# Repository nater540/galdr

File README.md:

# Galdr

**Galdr** is a compact desktop CNC milling system: custom [grblHAL](https://github.com/grblHAL)-compatible firmware
for an **ESP32-S3** motion controller, plus **skirnir**, a native desktop GCode sender that streams to it over USB.
It is general-purpose 2.5D/3-axis milling, with PCB isolation milling and no-touch-plate probing as a first-class
use case.

The firmware drives three stepper axes through silent [TMC2209](https://www.trinamic.com/) drivers and a WS55-220
spindle, speaks the grbl v1.1 / grblHAL streaming protocol, and is built around a strict hardware-abstraction boundary
so the entire motion pipeline — GCode parsing, look-ahead planning, the homing state machine, coordinate systems —
is pure `no_std` Rust that compiles and unit-tests on the host with stock Rust (600+ tests, no hardware required).

> *skirnir, the host-side GCode sender: the connection toolbar and state badge, the work/machine DRO and jog pad,
> feed/spindle/rapid overrides, a Z-probe panel, X/Y/Z endstop (`LIMITS`) indicators, the program console, and the
> toolpath viewport rendering a loaded program.*

---

## Workspace layout

Galdr is a Cargo workspace of four crates:

| Crate | Role |
|-------|------|
| [`crates/firmware-core`](crates/firmware-core) | Pure, `no_std`, **host-tested** logic: GCode parser, motion planner, segment generator, grblHAL protocol/state machine, the homing state machine, coordinate systems, settings model, and the TMC2209 codec. No esp-hal dependency. |
| [`crates/firmware`](crates/firmware) | The **ESP32-S3** binary wiring `firmware-core` to the hardware (esp-hal 1.0 + Embassy on the esp-rtos host): USB CDC comms, the dual-core task split, RMT step generation, the TMC UART bus, flash persistence, and the limit-switch inputs. |
| [`crates/galdr-proto`](crates/galdr-proto) | The shared Protocol Buffers schema (micropb) for the settings/coordinate wire format — used by both the firmware flash records and the `$PBX` host-sync channel. |
| [`crates/skirnir`](crates/skirnir) | The native GCode sender: an **egui/eframe** GUI on top of a framework-agnostic `tokio-serial` streaming engine. |

## Hardware

| Subsystem | Detail |
|-----------|--------|
| Controller | ESP32-S3 (Xtensa LX7), native USB Serial/JTAG to the host |
| Steppers | 3× X/Y/Z via TMC2209 on a shared single-wire UART bus (CRC8-ATM datagrams) |
| Step generation | One dedicated RMT TX channel per axis (ch0/1/2) |
| Endstops | Normally-closed micro-switches on GPIO10/11/12, internal pull-ups, broken-wire fail-safe |
| Spindle | WS55-220 via LEDC PWM → RC + op-amp → 0–10 V |

See [`docs/00-architecture.md`](docs/00-architecture.md) for the full hardware/GPIO manifest and firmware design
(DOC-00 – DOC-09).

## Status

The firmware (`firmware-core` + `firmware` + `galdr-proto`) is substantially implemented and host-tested:

- ✅ GCode → planner → motion pipeline (look-ahead, junction-deviation cornering, trapezoidal segment generation)
- ✅ grblHAL streaming protocol (character-counting flow control, real-time commands, `<...>` status reports)
- ✅ TMC2209 driver (current scaling, register init, CRC8-ATM)
- ✅ Settings + coordinate-system persistence (flash + `$PBX` host sync)
- ✅ G38.x probing, jogging, feed/rapid/spindle overrides
- ✅ `$H` homing cycle, hard/soft limits, and limit-switch `Pn:` status reporting (DOC-06)

**Not yet hardware-verified:** the DOC-06 homing/limit *logic* is fully host-tested, but its hardware boundary — the
rising-edge limit IRQ + debounce, the NC broken-wire fail-safe, and real seek/locate timing — is compile-checked only.
Run [`docs/homing-bench-checklist.md`](docs/homing-bench-checklist.md) on the board to validate it.

**Stubbed (logic exists, no peripheral output yet):** spindle PWM output (DOC-07) and the coolant GPIO.

skirnir is a working app: connection + reconnection, the streaming engine, `<...>`/`Pn:` status parsing, a DRO, jog
controls, override controls, a program console, and endstop indicators.

## Build & test

The workspace root is the repo root. Host crates build with stock Rust; the firmware needs the Espressif toolchain.

### Host (firmware-core, skirnir, galdr-proto)

```sh
cargo build                         # builds the host-buildable crates (firmware is excluded)
cargo test                          # host tests; add RUSTFLAGS="-D warnings" to match CI
cargo run -p skirnir                # launch the skirnir GUI
cargo run -p skirnir -- --cli <port>   # headless streaming smoke path
```

`firmware` is excluded from `default-members`, so the bare commands above stay on the host toolchain and skip it.
`--workspace`/`--all` override that — pass `--exclude firmware` with those flags.

### Firmware (ESP32-S3 / Xtensa LX7)

The Xtensa ISA needs Espressif's Rust fork:

```sh
cargo install espup
espup install
source $HOME/export-esp.sh          # source in every shell before firmware builds
```

The `justfile` wraps the toolchain env and the crate-scoped target/runner:

```sh
just build        # cargo build for Xtensa (e.g. `just build --release` / `--features defmt`)
just flash        # build + flash + serial monitor (espflash)
just monitor      # attach the serial monitor only
```

> See [`CLAUDE.md`](CLAUDE.md) for the full build notes, including the `esp-bootloader-esp-idf = "=0.4.0"` pin
> required with esp-hal 1.0.

## Design docs

`docs/` is the authoritative design spec — read the relevant doc before extending a subsystem.

| Doc | Covers |
|-----|--------|
| [`docs/00-architecture.md`](docs/00-architecture.md) | Full firmware spec (DOC-00 – DOC-09): hardware/GPIO manifest, Embassy task split, RMT step generation, TMC2209 driver, GCode parser, motion planner, homing, spindle, USB CDC, testing. **Start here.** |
| [`docs/gcode-streaming.md`](docs/gcode-streaming.md) | grblHAL streaming protocol: flow control, real-time commands, status reports, handshake, `$`-settings, probing. |
| [`docs/tlo-offsets.md`](docs/tlo-offsets.md) | Tool-length-offset / Z-probe workflow (G38.x, WPos/MPos/WCO/TLO) for no-touch-plate probing — single-tool re-zero and multi-tool reference-tool offsets (PCB isolation is one worked example). |
| [`docs/native-app.md`](docs/native-app.md) + [`docs/skirnir-design-brief.md`](docs/skirnir-design-brief.md) | skirnir design and UI brief (the source under `crates/skirnir/src/` is the truth). |
| [`docs/homing-research-findings.md`](docs/homing-research-findings.md) | The verified grblHAL homing/limit behavioral contract the implementation follows. |
| [`docs/homing-bench-checklist.md`](docs/homing-bench-checklist.md) | Hardware-in-the-loop bring-up procedure for the homing cycle + limit switches. |

## Conventions

- Two-space indentation (`.editorconfig`), LF endings, final newline.
- No `unwrap()`/`expect()` in library code; `#![deny(unsafe_code)]` in library crates; `#![deny(warnings)]` in CI.
- All hardware access goes behind traits (`StepSink`, `TmcBus`, `ProbeInput`, `DigitalIn`, …) so the logic stays
  host-testable; only the firmware wiring layer touches esp-hal.

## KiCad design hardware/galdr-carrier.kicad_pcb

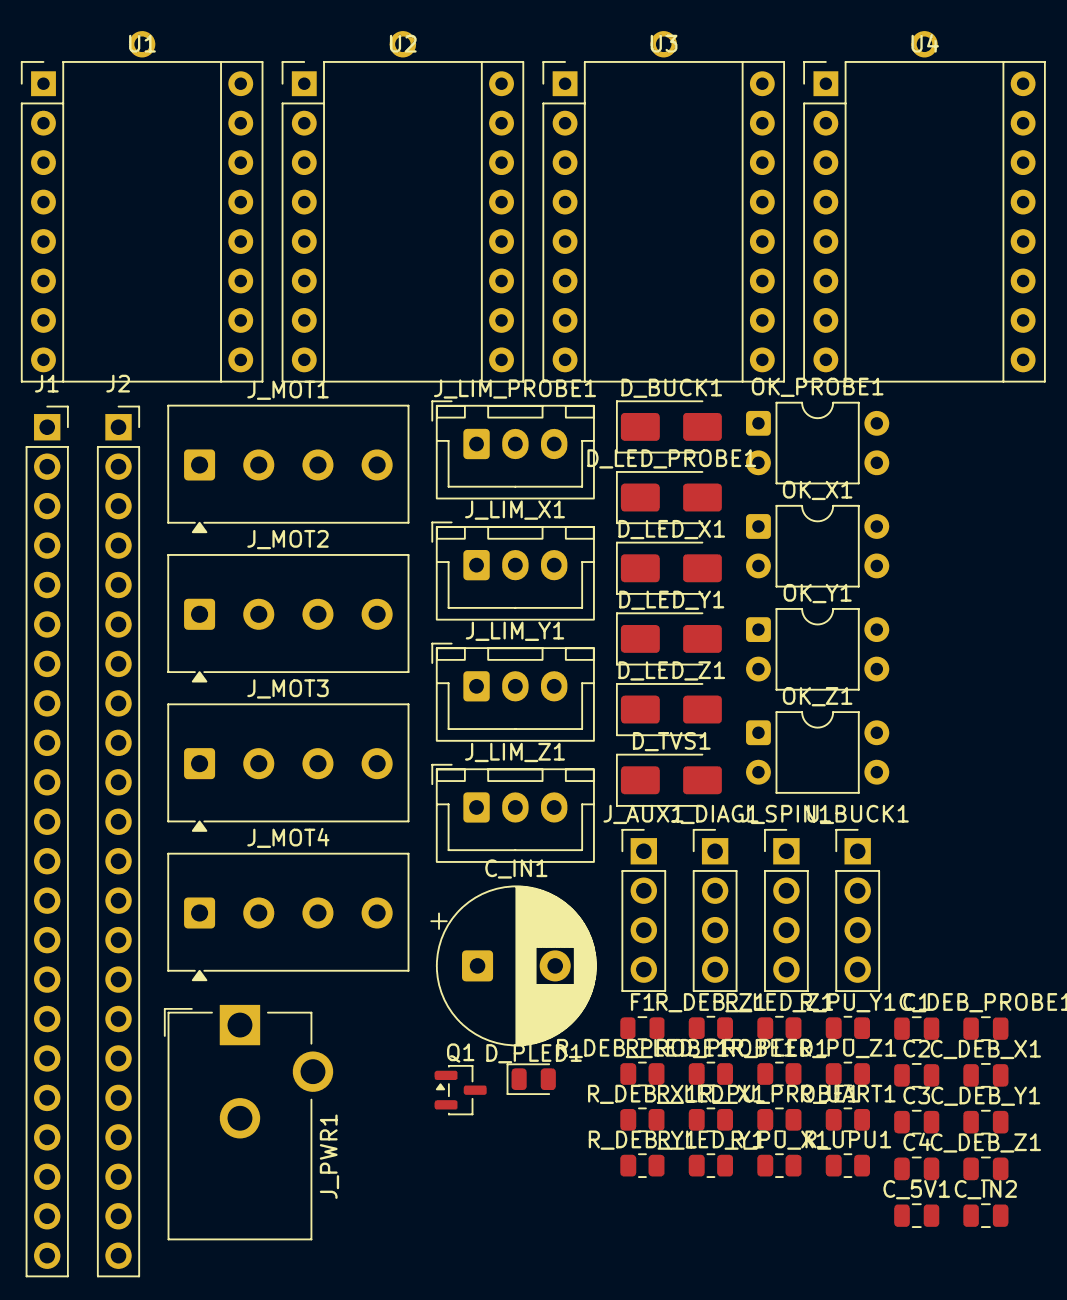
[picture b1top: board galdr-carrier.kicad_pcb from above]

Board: 2 copper layers, 58 parts (0 on the bottom side), 59 nets, no tracks yet.

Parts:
C1, C2, C3, C4: 100n; C_0805_2012Metric
C_5V1: 10u; C_0805_2012Metric
C_DEB_PROBE1: 100n; C_0805_2012Metric
C_DEB_X1: 100n; C_0805_2012Metric
C_DEB_Y1: 100n; C_0805_2012Metric
C_DEB_Z1: 100n; C_0805_2012Metric
C_IN1: 470u/35V; CP_Radial_D10.0mm_P5.00mm
C_IN2: 100n; C_0805_2012Metric
D_BUCK1: SS34; D_SMA
D_LED_PROBE1: 1N4148; D_SMA
D_LED_X1: 1N4148; D_SMA
D_LED_Y1: 1N4148; D_SMA
D_LED_Z1: 1N4148; D_SMA
D_PLED1: PWR; LED_0805_2012Metric
D_TVS1: SMAJ16A; D_SMA
F1: 3A; Fuse_0805_2012Metric
J1: ESP32-S3 DevBoard L; PinSocket_1x22_P2.54mm_Vertical
J2: ESP32-S3 DevBoard R; PinSocket_1x22_P2.54mm_Vertical
J_AUX1: AUX_CTRL; PinHeader_1x04_P2.54mm_Vertical
J_DIAG1: DIAG; PinHeader_1x04_P2.54mm_Vertical
J_LIM_PROBE1: LIM_PROBE; JST_XH_B3B-XH-A_1x03_P2.50mm_Vertical
J_LIM_X1: LIM_X; JST_XH_B3B-XH-A_1x03_P2.50mm_Vertical
J_LIM_Y1: LIM_Y; JST_XH_B3B-XH-A_1x03_P2.50mm_Vertical
J_LIM_Z1: LIM_Z; JST_XH_B3B-XH-A_1x03_P2.50mm_Vertical
J_MOT1: MOTOR_X; TerminalBlock_Phoenix_MKDS-1-4-3.81_1x04_P3.81mm_Horizontal
J_MOT2: MOTOR_Y; TerminalBlock_Phoenix_MKDS-1-4-3.81_1x04_P3.81mm_Horizontal
J_MOT3: MOTOR_Z; TerminalBlock_Phoenix_MKDS-1-4-3.81_1x04_P3.81mm_Horizontal
J_MOT4: MOTOR_A; TerminalBlock_Phoenix_MKDS-1-4-3.81_1x04_P3.81mm_Horizontal
J_PWR1: DC_12V_5.5x2.5; BarrelJack_CUI_PJ-102AH_Horizontal
J_SPIN1: SPINDLE; PinHeader_1x04_P2.54mm_Vertical
OK_PROBE1: PC817; DIP-4_W7.62mm
OK_X1: PC817; DIP-4_W7.62mm
OK_Y1: PC817; DIP-4_W7.62mm
OK_Z1: PC817; DIP-4_W7.62mm
Q1: AO3401(GSD); SOT-23
R_DEB_PROBE1: 1k; R_0805_2012Metric
R_DEB_X1: 1k; R_0805_2012Metric
R_DEB_Y1: 1k; R_0805_2012Metric
R_DEB_Z1: 1k; R_0805_2012Metric
R_LED_PROBE1: 680; R_0805_2012Metric
R_LED_X1: 680; R_0805_2012Metric
R_LED_Y1: 680; R_0805_2012Metric
R_LED_Z1: 680; R_0805_2012Metric
R_PLED1: 4k7; R_0805_2012Metric
R_PU_PROBE1: 10k; R_0805_2012Metric
R_PU_X1: 10k; R_0805_2012Metric
R_PU_Y1: 10k; R_0805_2012Metric
R_PU_Z1: 10k; R_0805_2012Metric
R_UART1: 1k; R_0805_2012Metric
R_UPU1: 20k; R_0805_2012Metric
U1, U2, U3, U4: BTT TMC2209 V1.3; TMC2209_StepStick_Socket
U_BUCK1: MP1584_12to5; PinHeader_1x04_P2.54mm_Vertical

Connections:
+3V3: J1.1 (3V3), J1.2 (3V3), J_AUX1.3, R_PU_PROBE1.1, R_PU_X1.1, R_PU_Y1.1, R_PU_Z1.1, R_UPU1.1, U1.10 (VIO), U2.2 (MS1), U2.10 (VIO), U3.3 (MS2), U3.10 (VIO), U4.2 (MS1), U4.3 (MS2), U4.10 (VIO)
+5V: C_5V1.1, D_BUCK1.1 (K), J1.21 (5V0)
+5V_BUCK: D_BUCK1.2 (A), U_BUCK1.3
+12V: C1.1, C2.1, C3.1, C4.1, C_IN1.1, C_IN2.1, D_TVS1.1 (A1), J_LIM_PROBE1.1, J_LIM_X1.1, J_LIM_Y1.1, J_LIM_Z1.1, R_LED_PROBE1.1, R_LED_X1.1, R_LED_Y1.1, R_LED_Z1.1, R_PLED1.1, U1.16 (VM), U2.16 (VM), U3.16 (VM), U4.16 (VM), U_BUCK1.1
A_A1: J_MOT4.1, U4.13 (A1)
A_A2: J_MOT4.2, U4.14 (A2)
A_B1: J_MOT4.3, U4.12 (B1)
A_B2: J_MOT4.4, U4.11 (B2)
A_DIAG: J_DIAG1.4, U4.17 (DIAG)
A_DIR: J2.6 (IO42), U4.8 (DIR)
A_STEP: J1.11 (IO18), U4.7 (STEP)
CYCSTART: J1.10 (IO17), J_AUX1.2
FHOLD: J1.9 (IO16), J_AUX1.1
GND: C1.2, C2.2, C3.2, C4.2, C_5V1.2, C_DEB_PROBE1.2, C_DEB_X1.2, C_DEB_Y1.2, C_DEB_Z1.2, C_IN1.2, C_IN2.2, D_PLED1.1 (K), D_TVS1.2 (A2), J1.22 (GND), J2.1 (GND), J2.21 (GND), J2.22 (GND), J_AUX1.4, J_LIM_PROBE1.3, J_LIM_X1.3, J_LIM_Y1.3, J_LIM_Z1.3, J_PWR1.2, J_SPIN1.4, OK_PROBE1.3, OK_X1.3, OK_Y1.3, OK_Z1.3, U1.2 (MS1), U1.3 (MS2), U1.6 (CLK), U1.9 (GND), U1.15 (GND), U2.3 (MS2), U2.6 (CLK), U2.9 (GND), U2.15 (GND), U3.2 (MS1), U3.6 (CLK), U3.9 (GND), U3.15 (GND), U4.6 (CLK), U4.9 (GND), U4.15 (GND), U_BUCK1.2, U_BUCK1.4
PLED_A: D_PLED1.2 (A), R_PLED1.2
PROBE: C_DEB_PROBE1.1, J2.18 (IO21), R_DEB_PROBE1.2
PROBE_COL: OK_PROBE1.4, R_DEB_PROBE1.1, R_PU_PROBE1.2
PROBE_LEDA: D_LED_PROBE1.1 (K), OK_PROBE1.1, R_LED_PROBE1.2
PROBE_SIG: D_LED_PROBE1.2 (A), J_LIM_PROBE1.2, OK_PROBE1.2
SPIN_DIR: J1.8 (IO15), J_SPIN1.3
SPIN_EN: J1.20 (IO14), J_SPIN1.2
SPIN_PWM: J1.19 (IO13), J_SPIN1.1
STEP_EN: J1.12 (IO8), U1.1 (EN), U2.1 (EN), U3.1 (EN), U4.1 (EN)
TMC_BUS: R_UART1.2, R_UPU1.2, U1.4 (RX), U1.5 (TX), U2.4 (RX), U2.5 (TX), U3.4 (RX), U3.5 (TX), U4.4 (RX), U4.5 (TX)
TMC_UART: J1.15 (IO9), R_UART1.1
VIN_RAW: F1.1, J_PWR1.1
X_A1: J_MOT1.1, U1.13 (A1)
X_A2: J_MOT1.2, U1.14 (A2)
X_B1: J_MOT1.3, U1.12 (B1)
X_B2: J_MOT1.4, U1.11 (B2)
X_COL: OK_X1.4, R_DEB_X1.1, R_PU_X1.2
X_DIAG: J_DIAG1.1, U1.17 (DIAG)
X_DIR: J1.5 (IO5), U1.8 (DIR)
X_LEDA: D_LED_X1.1 (K), OK_X1.1, R_LED_X1.2
X_LIM: C_DEB_X1.1, J1.16 (IO10), R_DEB_X1.2
X_SIG: D_LED_X1.2 (A), J_LIM_X1.2, OK_X1.2
X_STEP: J2.4 (IO1), U1.7 (STEP)
Y_A1: J_MOT2.1, U2.13 (A1)
Y_A2: J_MOT2.2, U2.14 (A2)
Y_B1: J_MOT2.3, U2.12 (B1)
Y_B2: J_MOT2.4, U2.11 (B2)
Y_COL: OK_Y1.4, R_DEB_Y1.1, R_PU_Y1.2
Y_DIAG: J_DIAG1.2, U2.17 (DIAG)
Y_DIR: J1.6 (IO6), U2.8 (DIR)
Y_LEDA: D_LED_Y1.1 (K), OK_Y1.1, R_LED_Y1.2
Y_LIM: C_DEB_Y1.1, J1.17 (IO11), R_DEB_Y1.2
Y_SIG: D_LED_Y1.2 (A), J_LIM_Y1.2, OK_Y1.2
Y_STEP: J2.5 (IO2), U2.7 (STEP)
Z_A1: J_MOT3.1, U3.13 (A1)
Z_A2: J_MOT3.2, U3.14 (A2)
Z_B1: J_MOT3.3, U3.12 (B1)
Z_B2: J_MOT3.4, U3.11 (B2)
Z_COL: OK_Z1.4, R_DEB_Z1.1, R_PU_Z1.2
Z_DIAG: J_DIAG1.3, U3.17 (DIAG)
Z_DIR: J1.7 (IO7), U3.8 (DIR)
Z_LEDA: D_LED_Z1.1 (K), OK_Z1.1, R_LED_Z1.2
Z_LIM: C_DEB_Z1.1, J1.18 (IO12), R_DEB_Z1.2
Z_SIG: D_LED_Z1.2 (A), J_LIM_Z1.2, OK_Z1.2
Z_STEP: J1.4 (IO4), U3.7 (STEP)

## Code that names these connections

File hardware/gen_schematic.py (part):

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           ref_xy=(EOX - 13, EOY - 36), val_xy=(EOX - 13, EOY - 33.5))
# pin number -> net  ('' => power port handled below, None entries => no_connect)
ESP_SIG = {  # left column
    "4": "Z_STEP", "5": "X_DIR", "6": "Y_DIR", "7": "Z_DIR", "8": "SPIN_DIR", "9": "FHOLD",
    "10": "CYCSTART", "11": "A_STEP", "12": "STEP_EN", "15": "TMC_UART", "16": "X_LIM",
    "17": "Y_LIM", "18": "Z_LIM", "19": "SPIN_PWM", "20": "SPIN_EN",
    # right column
    "26": "X_STEP", "27": "Y_STEP", "28": "A_DIR", "40": "PROBE"}
ESP_PWR = {"1": "+3V3", "2": "+3V3", "21": "+5V", "22": "GND", "23": "GND", "43": "GND", "44": "GND"}
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    t = place("Galdr:BTT_TMC2209", f"U{i+1}", "BTT TMC2209 V1.3", FP_TMC, ox, oy,
              ref_xy=(ox - 7, oy - 20.5), val_xy=(ox - 7, oy - 18))
    # left side: control signals + straps (stub left, then label/port)
    seg(*t["1"], t["1"][0] - 2.54, t["1"][1]); glabel("STEP_EN", t["1"][0] - 2.54, t["1"][1], 180)   # EN
    for strap_num in ("2", "3"):                                                                       # MS1/MS2
        seg(*t[strap_num], t[strap_num][0] - 2.54, t[strap_num][1]); pwr(ms[strap_num], t[strap_num][0] - 2.54, t[strap_num][1])
    # RX (4) + TX (5) both join the single-wire UART bus
    seg(*t["4"], t["4"][0] - 2.54, t["4"][1]); glabel("TMC_BUS", t["4"][0] - 2.54, t["4"][1], 180)
    seg(*t["5"], t["5"][0] - 2.54, t["5"][1]); glabel("TMC_BUS", t["5"][0] - 2.54, t["5"][1], 180)
    seg(*t["6"], t["6"][0] - 2.54, t["6"][1]); pwr("GND", t["6"][0] - 2.54, t["6"][1])                 # CLK -> GND
    seg(*t["7"], t["7"][0] - 2.54, t["7"][1]); glabel(f"{ax}_STEP", t["7"][0] - 2.54, t["7"][1], 180)
    seg(*t["8"], t["8"][0] - 2.54, t["8"][1]); glabel(f"{ax}_DIR", t["8"][0] - 2.54, t["8"][1], 180)
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# ---- TMC UART: series resistor to the bus + idle pull-up to +3V3 -------------
# R_UART converts the half-duplex single-wire UART; R_UPU idles the bus high. Both tie to the TMC_BUS node.
ru = place("Device:R", "R_UART", "1k", FP_R, 220, 56, 90)     # horizontal: pin2 left, pin1 right
seg(*ru["2"], ru["2"][0] - 2.54, ru["2"][1]); glabel("TMC_UART", ru["2"][0] - 2.54, ru["2"][1], 180)
rp = place("Device:R", "R_UPU", "20k", FP_R, 220, 48)         # vertical: pin1 top -> +3V3, pin2 bottom -> bus
seg(*rp["1"], rp["1"][0], rp["1"][1] - 2.54); pwr("+3V3", rp["1"][0], rp["1"][1] - 2.54)
# TMC_BUS node: join R_UART pin1 (right) and R_UPU pin2 (bottom) and emit a global label.
busx = ru["1"][0] + 2.54
seg(ru["1"][0], ru["1"][1], busx, ru["1"][1])
seg(rp["2"][0], rp["2"][1], rp["2"][0], ru["1"][1])
seg(rp["2"][0], ru["1"][1], busx, ru["1"][1])
junction(rp["2"][0], ru["1"][1])
glabel("TMC_BUS", busx, ru["1"][1], 0)

# ---- opto-isolated inputs: X / Y / Z limits + PROBE ------------------------
# Per channel: a field connector drives the PC817 LED through a current-limit resistor (anti-parallel signal diode
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    seg(*cdb["2"], cdb["2"][0], cdb["2"][1] + 2.54); pwr("GND", cdb["2"][0], cdb["2"][1] + 2.54)
    glabel(gpio_net, gpiox, col[1], 0)

for i, (ref, gpio) in enumerate([("X", "X_LIM"), ("Y", "Y_LIM"), ("Z", "Z_LIM"), ("PROBE", "PROBE")]):
    opto_channel(40 + i * 135, 190, gpio, ref)

# ---- power input: 12 V jack -> fuse -> reverse-protect PFET -> +12V rail -> buck -> +5V ----
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# -- jack + fuse + PFET feeding the rail --
jp = place("Connector:Barrel_Jack", "J_PWR", "DC_12V_5.5x2.5", FP_JACK, 40, 300)
seg(*jp["2"], jp["2"][0], PGY); junction(jp["2"][0], PGY)     # jack sleeve -> GND rail
f1 = place("Device:Fuse", "F1", "3A", FP_FUSE, 54, 297.46, 270)   # pin1 VIN_RAW left, pin2 VIN_F right
elbow(jp["1"], f1["1"])
q1 = place("Device:Q_PMOS", "Q1", "FQP27P06", FP_FET, 68, 300)    # D top=VIN_F, S bottom=+12V, G left=GND
elbow(f1["2"], q1["D"], hfirst=False)
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# J_SPIN carries the spindle conditioning signals + 12 V to the daughterboard (page 2); J_AUX exposes feed-hold /
# cycle-start. Both are pin headers; signals leave as global labels (buses to the ESP32 / page 2).
sp = place("Connector_Generic:Conn_01x06", "J_SPIN", "SPINDLE_IF", FP_JST6, 470, 150)
for num, net in (("1", "SPIN_PWM"), ("2", "SPIN_EN"), ("3", "SPIN_DIR"), ("4", "+12V"), ("5", "GND"), ("6", "GND")):
    seg(*sp[num], sp[num][0] - 2.54, sp[num][1])
    if net in POWER_NETS:
        pwr(net, sp[num][0] - 2.54, sp[num][1])
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
# inter-board input connector (mates J_SPIN); pins face right into the circuit.
ci = place("Connector_Generic:Conn_01x06", "J_CIN", "FROM_CARRIER", FP_JST6, 30, 74, 180)
ci_net = {"1": "SPIN_PWM", "2": "SPIN_EN", "3": "SPIN_DIR", "4": "+12V", "5": "GND", "6": "GND"}
for num, net in ci_net.items():
    seg(*ci[num], ci[num][0] + 2.54, ci[num][1])
    if net in POWER_NETS:
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# no flag is added here (a second flag on the same global rail would be a duplicate power source).

# PWM -> DC: two-stage RC low-pass into SP_DC.
rl1 = place("Device:R", "R_LP1", "10k", FP_R, 52, 66, 90)        # pin2 left=SPIN_PWM, pin1 right=SP_LP1
seg(*rl1["2"], rl1["2"][0] - 2.54, rl1["2"][1]); glabel("SPIN_PWM", rl1["2"][0] - 2.54, rl1["2"][1], 180)
rl2 = place("Device:R", "R_LP2", "10k", FP_R, 66, 66, 90)        # pin2 left=SP_LP1, pin1 right=SP_DC
seg(rl1["1"][0], rl1["1"][1], rl2["2"][0], rl2["2"][1])          # SP_LP1 node
cl1 = place("Device:C", "C_LP1", "1u", FP_C, rl1["1"][0], 74)    # SP_LP1 -> GND
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    seg(rpd["2"][0], rpd["2"][1], rpd["2"][0], rpd["2"][1] + 2.54); pwr("GND", rpd["2"][0], rpd["2"][1] + 2.54)
    seg(*qn["S"], qn["S"][0], qn["S"][1] + 2.54); pwr("GND", qn["S"][0], qn["S"][1] + 2.54)
    seg(*qn["D"], qn["D"][0], qn["D"][1] - 2.54); glabel(drv_net, qn["D"][0], qn["D"][1] - 2.54, 90)
driver(58, "SPIN_EN", "SP_GE", "SP_ENDRV", "R_GE", "R_PDE", "Q_EN")
driver(96, "SPIN_DIR", "SP_GD", "SP_DIRDRV", "R_GD", "R_PDD", "Q_DIR")

# output terminal block to the WS55-220.
ws = place("Connector_Generic:Conn_01x04", "J_WS", "TO_WS55-220", FP_TERM4, 175, 120)
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
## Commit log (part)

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2026-06-16 Wrapping up gcode streaming
2026-06-17 Starting work on skirnir app
2026-06-17 Starting initial work on Skirnir
2026-06-17 Skirnir bug fixes
2026-06-18 Fixed skirnir black vertical bar; tweaked settings dialog
2026-06-18 Initial homing pass support
2026-06-18 Exposing endstop statuses via `Pn` output
2026-06-18 Documentation updates
2026-06-18 Expand error handling a bit futher - uses grblHAL `[MSG...]`
2026-06-18 Bug fixes
2026-06-18 More bug fixes
2026-06-21 Working on 4th axis support
2026-06-21 Working on 4th axis
2026-06-21 Prevent movement while probing A
2026-06-22 Skirnir rotary work
2026-06-22 Doc updates
2026-06-22 Small bug fix with TMC drivers
2026-06-24 Upgrade completed and verified
2026-06-25 Split kitematics from firmware-core to allow skirnir to create somewhat realistic ETAs
2026-06-25 Initial app config setup
2026-06-26 Tweaked colors + no longer drawing rapids to reduce clutter
2026-06-27 Trying to get firmware to work over longer periods of time
2026-06-29 Trying to narrow down hardware fault
2026-06-29 Fixed feed override sliders + re-added MDI input
2026-06-30 Added localization because why not
